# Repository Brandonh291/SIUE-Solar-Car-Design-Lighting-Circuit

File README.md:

# SIUE-Solar-Car-Design-Lighting-Circuit
Solar Car Lighting Circuit
Lighting Controller MCU specifications

Read through section 9.4 of the 2020 regulations for how the external lights should behave.

Also, download the orion bms wiring sheet, it’ll be useful.

· The lighting controller will dictate when a light on the car turns on and off

· It will control 10 exterior lights

o Two forward facing headlights

o Two forward facing blinkers

o Two lateral blinkers

o Three rear lights, two of which are blinker/break and one of which is a break light

o One BPS trip strobe

· The behavior of the lights is as follows:

o The headlights will be controlled by a toggle switch. When the switch is closed, the headlights will turn on. When the switch is opened the headlights will turn off.

o The blinkers will be controlled by a three-state toggle switch. When the switch is turned left, the forward, lateral, and rear left lights will begin blinking. The same for if the switch is turned right. If the switch is neutral, no blinking will occur.

o The brakes will illuminate when the brake petal is depressed. Two of the three brake lights in the rear of the vehicle will also function as blinkers. When the blinkers and brakes are engaged, the blinkers take priority.

o The hazard will be controlled by a toggle switch. When it is closed, all lights except for the BPS strobe will flash until the switch is opened.

o The BPS strobe is controlled by an open drain output from the Orion BMS. Normal, working conditions will set the output high. When the device detects a battery fault, the output goes low. See the “Digital Signal outputs” section in the Orion BMS wiring manual for more information.

· Power requirements

o Each LED strip burns about 50mA at 12V, so whatever is used to switch them must be capable of handling this load. In the case of the headlights, and each front/lateral set of blinkers, are tied together, so the switch powering them must be able to handle approximately 100mA. There are logic level FETs that can drive the LEDs.

o I want input protection on the switches to make it ESD resistant. A google search for “MCU input protection” will yield plenty of results.

· Hardware and I/O

o It’d be nice if the I/O was confined to a single connector like a D-sub connector or something similar to confine all the connections to a single plug.

Parts List
  * 14 - 3.5mm 2 Pin Screw Terminal Block
  * 7 - 10k Resistors
  * 7 - 2k Resistors
  * 1 - 1M Resistor
  * 1 - Arduino Nano Microcontroller
  * 7 - RFP30N06LE Mosfets
  * 2 - 74HC08N Quad 2 Input AND IC
  * 1 - 74LS04N Hex Inverter IC
  * 1 - 74HC32N Quad 2 Input OR IC
  * 1 - NE555N Timer
  * 1 - 470nF Capacitor
  * 1 - 10nF Capacitor

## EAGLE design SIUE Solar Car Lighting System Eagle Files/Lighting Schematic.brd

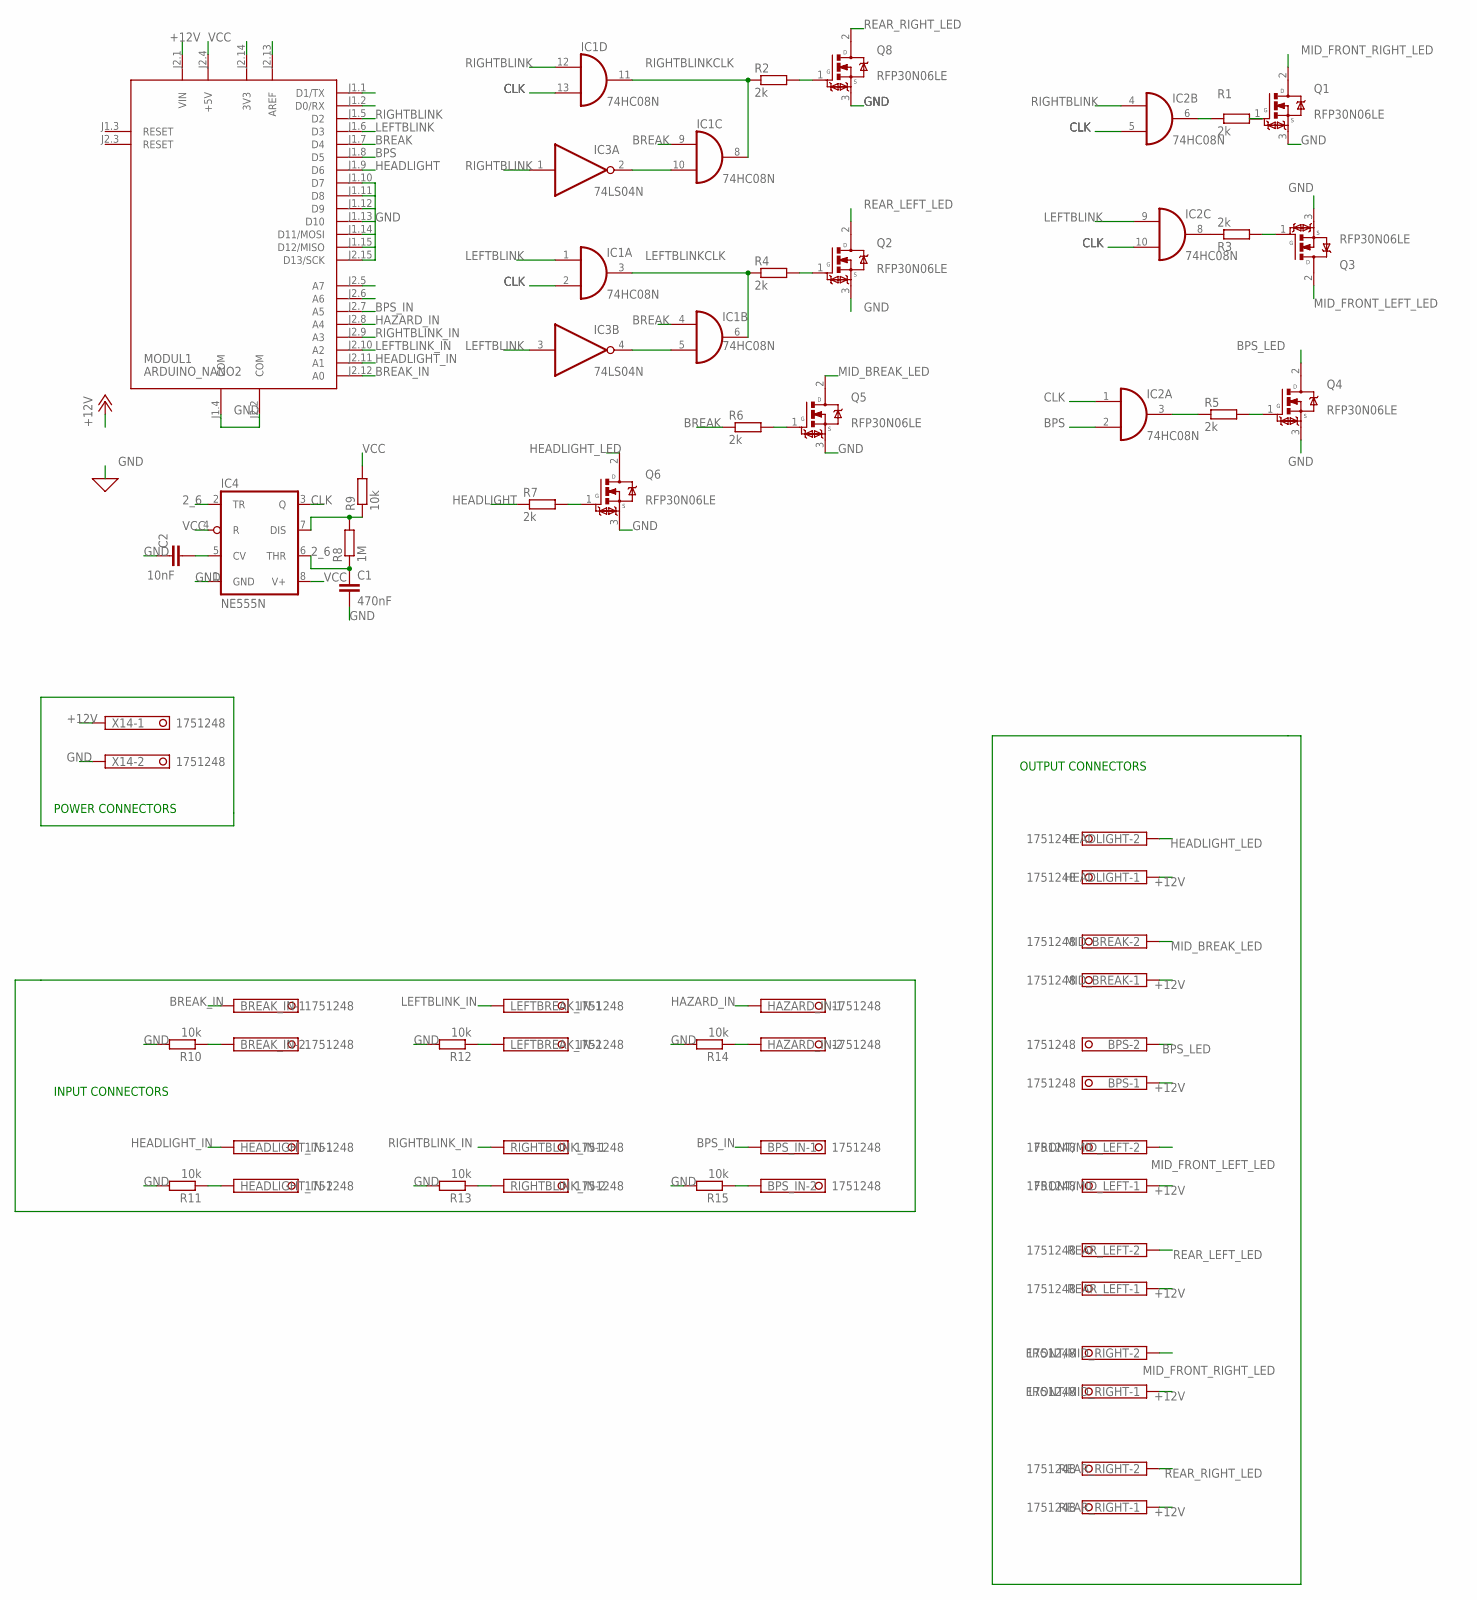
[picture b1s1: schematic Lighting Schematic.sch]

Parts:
BPS: 1751248
BPS_IN: 1751248
BREAK_IN: 1751248
C1: 470nF; C2.5-2
C2: 10nF; C2.5-2
FRONT/MID_LEFT: 1751248
FRONT/MID_RIGHT: 1751248
HAZARD_IN: 1751248
HEADLIGHT: 1751248
HEADLIGHT_IN: 1751248
IC1, IC2: 74HC08N; DIL14
IC3: 74LS04N; DIL14
IC4: NE555N; DIL08
LEFTBREAK_IN: 1751248
MID_BREAK: 1751248
MODUL1: ARDUINO_NANO2
Q1, Q2, Q3, Q4, Q5, Q6, Q8: RFP30N06LE; TRANS_RFP30N06LE
R1, R2, R3, R4, R5, R6, R7: 2k; 0204/5
R8: 1M; 0204/5
R9, R10, R11, R12, R13, R14, R15: 10k; 0204/5
REAR_LEFT: 1751248
REAR_RIGHT: 1751248
RIGHTBLINK_IN: 1751248
X14: 1751248

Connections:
2_6: C1.1, IC4.2 (TR), IC4.6 (THR), R8.1
+12V: BPS.1, FRONT/MID_LEFT.1, FRONT/MID_RIGHT.1, HEADLIGHT.1, MID_BREAK.1, MODUL1.J2.1 (VIN), REAR_LEFT.1, REAR_RIGHT.1, X14.1
BPS: IC2.2 (I1), MODUL1.J1.8 (D5)
BPS_IN: BPS_IN.1, MODUL1.J2.7 (A5)
BPS_LED: BPS.2, Q4.2 (D)
BREAK: IC1.4 (I0), IC1.9 (I0), MODUL1.J1.7 (D4), R6.1
BREAK_IN: BREAK_IN.1, MODUL1.J2.12 (A0)
CLK: IC1.2 (I1), IC1.13 (I1), IC2.1 (I0), IC2.5 (I1), IC2.10 (I1), IC4.3 (Q)
GND: C1.2, C2.1, IC1.7 (GND), IC2.7 (GND), IC3.7 (GND), IC4.1 (GND), MODUL1.J1.4 (COM), MODUL1.J1.10 (D7), MODUL1.J2.2 (COM), MODUL1.J2.15 (D13/SCK), Q1.3 (S), Q2.3 (S), Q3.3 (S), Q4.3 (S), Q5.3 (S), Q6.3 (S), Q8.3 (S), R10.2, R11.2, R12.2, R13.2, R14.2, R15.2, X14.2
HAZARD_IN: HAZARD_IN.1, MODUL1.J2.8 (A4)
HEADLIGHT: MODUL1.J1.9 (D6), R7.1
HEADLIGHT_IN: HEADLIGHT_IN.1, MODUL1.J2.11 (A1)
HEADLIGHT_LED: HEADLIGHT.2, Q6.2 (D)
LEFTBLINK: IC1.1 (I0), IC2.9 (I0), IC3.3 (I), MODUL1.J1.6 (D3)
LEFTBLINKCLK: IC1.3 (O), IC1.6 (O), R4.1
LEFTBLINK_IN: LEFTBREAK_IN.1, MODUL1.J2.10 (A2)
MID_BREAK_LED: MID_BREAK.2, Q5.2 (D)
MID_FRONT_LEFT_LED: FRONT/MID_LEFT.2, Q3.2 (D)
MID_FRONT_RIGHT_LED: FRONT/MID_RIGHT.2, Q1.2 (D)
unnamed: Q8.1 (G), R2.2
unnamed: IC1.10 (I1), IC3.2 (O)
unnamed: IC2.6 (O), R1.1
unnamed: IC1.5 (I1), IC3.4 (O)
unnamed: IC4.7 (DIS), R8.2, R9.1
unnamed: Q2.1 (G), R4.2
unnamed: Q1.1 (G), R1.2
unnamed: Q3.1 (G), R3.2
unnamed: Q4.1 (G), R5.2
unnamed: IC2.3 (O), R5.1
unnamed: Q5.1 (G), R6.2
unnamed: Q6.1 (G), R7.2
unnamed: IC2.8 (O), R3.1
unnamed: C2.2, IC4.5 (CV)
unnamed: BREAK_IN.2, R10.1
unnamed: HEADLIGHT_IN.2, R11.1
unnamed: LEFTBREAK_IN.2, R12.1
unnamed: R13.1, RIGHTBLINK_IN.2
unnamed: HAZARD_IN.2, R14.1
unnamed: BPS_IN.2, R15.1
REAR_LEFT_LED: Q2.2 (D), REAR_LEFT.2
REAR_RIGHT_LED: Q8.2 (D), REAR_RIGHT.2
RIGHTBLINK: IC1.12 (I0), IC2.4 (I0), IC3.1 (I), MODUL1.J1.5 (D2)
RIGHTBLINKCLK: IC1.8 (O), IC1.11 (O), R2.1
RIGHTBLINK_IN: MODUL1.J2.9 (A3), RIGHTBLINK_IN.1
VCC: IC1.14 (VCC), IC2.14 (VCC), IC3.14 (VCC), IC4.4 (R), IC4.8 (V+), MODUL1.J2.4 (+5V), R9.2

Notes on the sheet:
INPUT CONNECTORS
OUTPUT CONNECTORS
POWER CONNECTORS

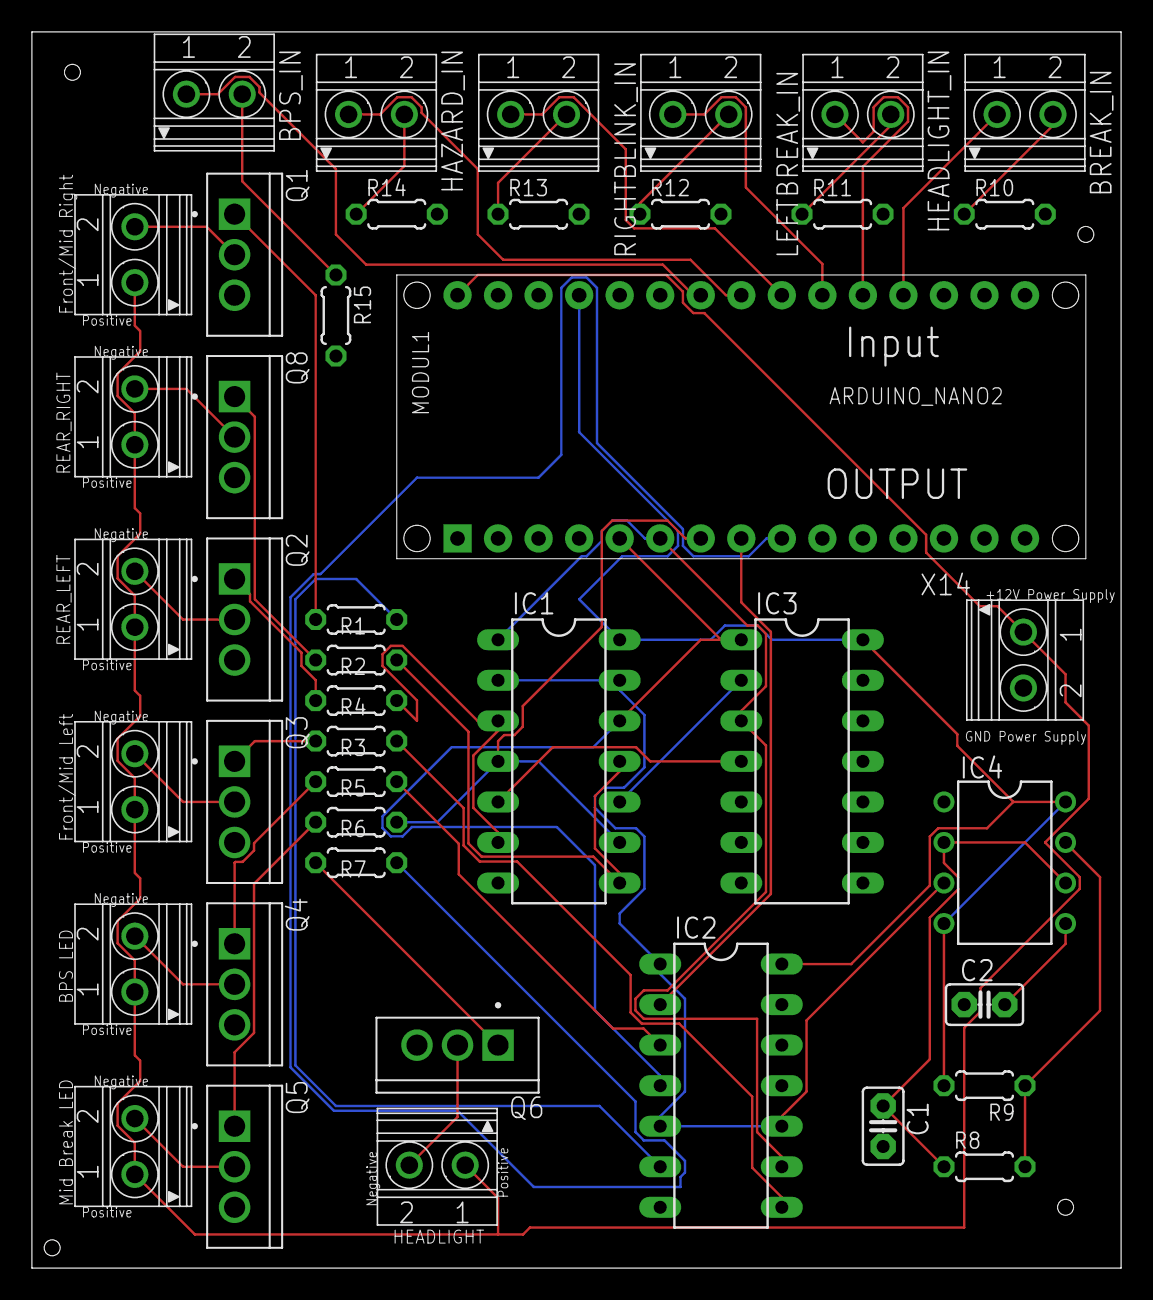
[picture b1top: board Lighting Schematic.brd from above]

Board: 2 copper layers, 68.2 x 77.5 mm, 43 parts (0 on the bottom side), 45 nets.

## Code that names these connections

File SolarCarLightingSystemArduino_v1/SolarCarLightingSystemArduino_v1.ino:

////////////////////////////////////////////////////////////////////////////////////////////////////////////////////
////////////////////////////////////////////////////////////////////////////////////////////////////////////////////
// By: Brandon Hickey
// SIUE SOLAR CAR DESIGN
// Date: 10/21/2019
////////////////////////////////////////////////////////////////////////////////////////////////////////////////////
// Description: 
// All of the input and output pins are hard-coded to the PCB design.
// So if you change the PCB you will need to change these hard-coded values and vice versa.
// The code simply goes through and reads all input pins and makes the corresponding changes on the output
////////////////////////////////////////////////////////////////////////////////////////////////////////////////////
////////////////////////////////////////////////////////////////////////////////////////////////////////////////////

void setup() 
{
  /////////////////////////////
  // Input Pins
    int BPS_IN=A5;
    int HAZARD_IN=A4;
    int RIGHTBLINK_IN=A3;
    int LEFTBLINK_IN=A2;
    int HEADLIGHT_IN=A1;
    int BREAK_IN=A0;
  // Input Pin Setup
    pinMode(BPS_IN,INPUT);
    pinMode(HAZARD_IN,INPUT);
    pinMode(RIGHTBLINK_IN,INPUT);
    pinMode(LEFTBLINK_IN,INPUT);
    pinMode(HEADLIGHT_IN,INPUT);
    pinMode(BREAK_IN,INPUT);
  /////////////////////////////

  /////////////////////////////
  // Output Pins
    int RIGHTBLINK=2;
    int LEFTBLINK=3;
    int BREAK=4;
    int BPS=5;
    int HEADLIGHT=6;
  // Output Pin Setup
    pinMode(RIGHTBLINK,OUTPUT);
    pinMode(LEFTBLINK,OUTPUT);
    pinMode(BREAK,OUTPUT);
    pinMode(BPS,OUTPUT);
    pinMode(HEADLIGHT,OUTPUT);
  /////////////////////////////
}


void loop() {
  /////////////////////////////
  // Read Pins and Send Signals
    checkRightTurn();
    checkLeftTurn();
    checkBreak();
    checkBPS();
    checkHeadlight();
  /////////////////////////////
}


void checkRightTurn()
{
  /////////////////////////////
  // Description:
  // Read the signal coming from the hazard and right blink switch, if either are HIGH(~5V) turn the RIGHTBLINK output pin HIGH
  // If neither are high then go LOW (~0V)
  // Inputs(Pin):
  //    HAZARD_IN(A4)
  //    RIGHTBLINK_IN(A3)
  // Outputs(Pin):
  //    RIGHTBLINK(2)
  /////////////////////////////
  if(digitalRead(HAZARD_IN)==1 || digitalRead(RIGHTBLINK_IN)==1){
    digitalWrite(RIGHTBLINK,HIGH);
  }
  else{
    digitalWrite(RIGHTBLINK,LOW); //else goes low
  }
}


void checkLeftTurn()
{
  /////////////////////////////
  // Description:
  // Read the signal coming from the hazard and left blink switch, if either are HIGH(~5V) turn the LEFTBLINK output pin HIGH
  // If neither are high then go LOW (~0V)
  // Inputs(Pin):
  //    HAZARD_IN(A4)
  //    LEFTBLINK_IN(A2)
  // Outputs(Pin):
  //    LEFTBLINK(3)
  /////////////////////////////
  if(digitalRead(HAZARD_IN)==1 || digitalRead(LEFTBLINK_IN)==1){
    digitalWrite(LEFTBLINK,HIGH);
  }
  else{
    digitalWrite(LEFTBLINK,LOW);
  }
}


void checkBreak()
{
  /////////////////////////////
  // Description:
  // Read the signal coming from the break switch, if HIGH(~5V) turn the BREAK output pin HIGH
  // Else go LOW (~0V)
  // Inputs(Pin):
  //    BREAK_IN(A0)
  // Outputs(Pin):
  //    BREAK(4)
  /////////////////////////////
  if(digitalRead(BREAK_IN)==1){
    digitalWrite(BREAK,HIGH);
  }
  else{
    digitalWrite(BREAK,LOW);
  }
}


checkBPS()
{
  /////////////////////////////
  // Description:
  // Read the signal coming from the BPS pin, if LOW(~0V) turn the BPS output pin HIGH
  // if HIGH(~5V) input, turn BPS output pin LOW
  // Inputs(Pin):
  //    BPS_IN(A5)
  // Outputs(Pin):
  //    BPS(5)
  /////////////////////////////
  if(digitalRead(BPS_IN)==0){
    digitalWrite(BPS,HIGH);
  }
  else{
    digitalWrite(BPS,LOW);
  }
}


checkHeadlight()
{
  /////////////////////////////
  // Description:
  // Read the signal coming from the headlight switch, if HIGH(~5V) turn the HEADLIGHT output pin HIGH
  // Else go LOW (~0V)
  // Inputs(Pin):
  //    HEADLIGHT_IN(A1)
  // Outputs(Pin):
  //    HEADLIGHT(6)
  /////////////////////////////
  if(digitalRead(HEADLIGHT_IN)==1){
    digitalWrite(HEADLIGHT,HIGH);
  }
  else{
    digitalWrite(HEADLIGHT,LOW);
  }
}

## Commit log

2020-01-19 Add files via upload
    Several changes made in this version:
    - For the input connections I created an on-board 5V source on the positive end of the Input connector, and then a 10k pull-down resistor connected to the arduino on the other. This should make sure 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
    - This 5V source is included on the BPS_IN connector to allow for testing, in practical use since the BMS will be sending an HIGH Output when functioning correctly and go LOW when error is detected w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
2020-01-19 Rename Lighting Schematic.brd to Lighting Schematic Board.brd
    Edit name
2020-01-19 Rename Lighting Schematic.sch to Lighting Schematic Design.sch
2020-01-19 Delete Lighting Schematic_2020-01-19 CAM Files.zip
    RS-274
2020-01-19 Add files via upload
    Information about the competition and systems in use.
2020-01-19 Update README.md
    Added Parts List
